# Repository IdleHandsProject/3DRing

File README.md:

3DRing
======

3DRing Computer input device.

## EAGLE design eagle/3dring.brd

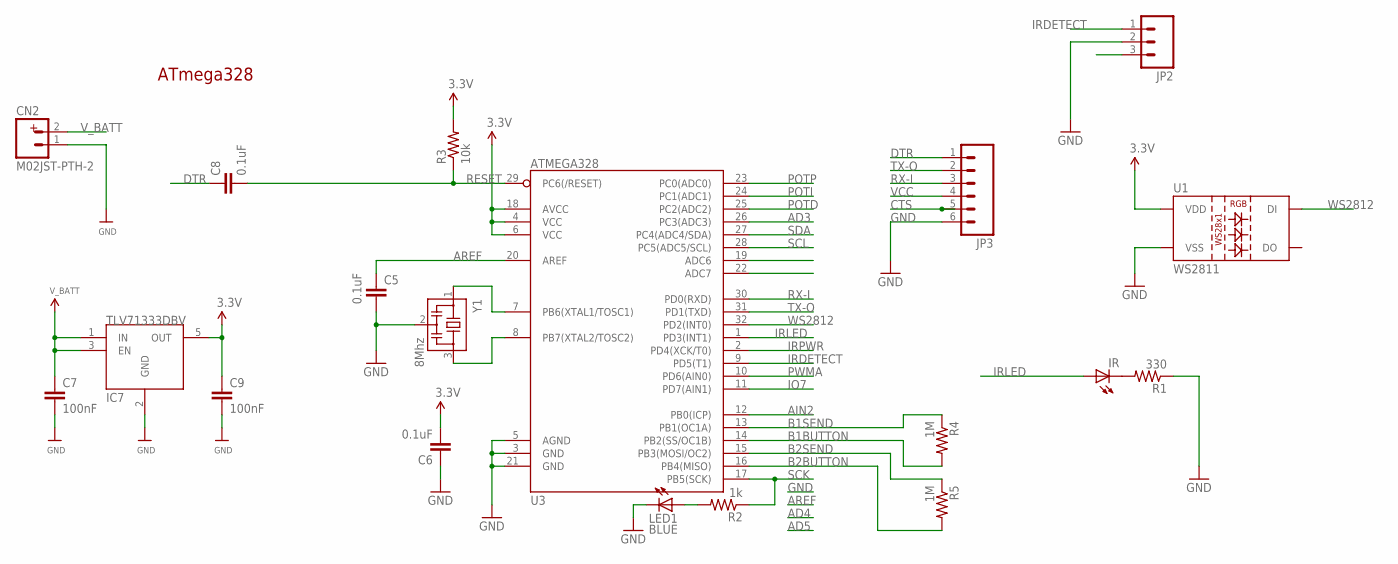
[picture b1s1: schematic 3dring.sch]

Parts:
C5, C6, C8: 0.1uF; 0402-CAP
C7, C9: 100nF; C0402
CN2: M02JST-PTH-2; JST-2-PTH
IC7: TLV71333DBV; SOT-23-5
IR: LED5MM
JP2: M03PTH; 1X03
JP3: M06SMD-1MM; 1X06-1MM
LED1: BLUE; LED-0603
R1: 330; 0402-RES
R2: 1k; 0402-RES
R3: 10k; 0402-RES
R4, R5: 1M; 0402-RES
U1: WS2811; LED-TRICOLOR-5050-IC
U3: ATMEGA328; TQFP32-08
Y1: 8Mhz; CSTCR6M

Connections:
AD3: U3.26 (PC3(ADC3))
AIN2: U3.12 (PB0(ICP))
AREF: C5.1, U3.20 (AREF)
B1BUTTON: R4.2, U3.14 (PB2(SS/OC1B))
B1SEND: R4.1, U3.13 (PB1(OC1A))
B2BUTTON: R5.2, U3.16 (PB4(MISO))
B2SEND: R5.1, U3.15 (PB3(MOSI/OC2))
CTS: JP3.5
DTR: C8.1, JP3.1
GND: C5.2, C6.1, C7.2, C9.2, CN2.1, IC7.2 (GND), JP2.2, JP3.6, LED1.C, R1.1, U1.6 (VSS), U3.3 (GND), U3.5 (AGND), U3.21 (GND), Y1.2
IO7: U3.11 (PD7(AIN1))
IRDETECT: JP2.1, U3.9 (PD5(T1))
IRLED: IR.A, U3.1 (PD3(INT1))
IRPWR: JP2.3, U3.2 (PD4(XCK/T0))
unnamed: LED1.A, R2.2
unnamed: IR.K (C), R1.2
unnamed: U3.7 (PB6(XTAL1/TOSC1)), Y1.1
unnamed: U3.8 (PB7(XTAL2/TOSC2)), Y1.3
POTD: U3.25 (PC2(ADC2))
POTI: U3.24 (PC1(ADC1))
POTP: U3.23 (PC0(ADC0))
PWMA: U3.10 (PD6(AIN0))
RESET: C8.2, R3.1, U3.29 (PC6(/RESET))
RX-I: JP3.3, U3.30 (PD0(RXD))
SCK: R2.1, U3.17 (PB5(SCK))
SCL: U3.28 (PC5(ADC5/SCL))
SDA: U3.27 (PC4(ADC4/SDA))
TX-O: JP3.2, U3.31 (PD1(TXD))
VCC: C6.2, C9.1, IC7.5 (OUT), JP3.4, R3.2, U1.3 (VDD), U1.5 (VDD), U3.4 (VCC), U3.6 (VCC), U3.18 (AVCC)
V_BATT: C7.1, CN2.2, IC7.1 (IN), IC7.3 (EN)
WS2812: U1.2 (DI), U3.32 (PD2(INT0))

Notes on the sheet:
ATmega328

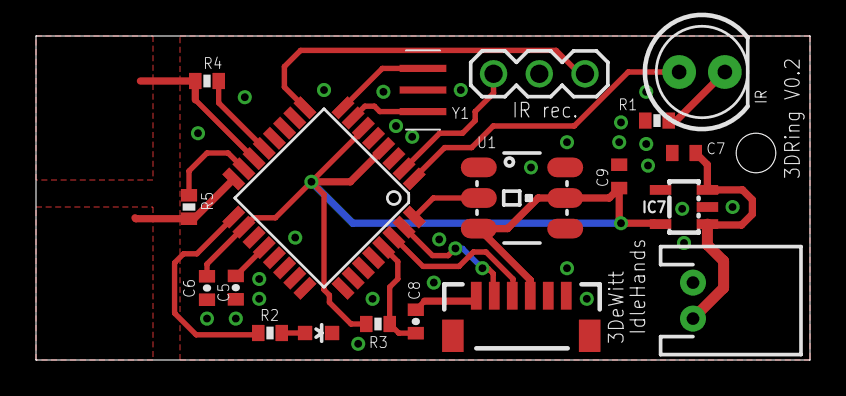
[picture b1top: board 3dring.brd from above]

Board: 2 copper layers, 43.0 x 18.0 mm, 19 parts (0 on the bottom side), 21 nets.

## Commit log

2014-06-18 Initial push
2014-06-30 Added cad files
2014-08-18 New ring design and pcb added
2014-08-19 board file added and ordered
2014-09-09 Latest Firmware before trip
2014-09-09 Updated board problems
2016-01-16 New version

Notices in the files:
parts and their libraries:
SparkFun-Connectors: Licensing: CC v3.0 Share-Alike You are welcome to use this library for commercial purposes.
